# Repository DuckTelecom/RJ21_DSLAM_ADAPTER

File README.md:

# RJ21_DSLAM_ADAPTER

This is an adapter / breakout aimed for use with the Zyxel AAM1212 DSLAM modules used in the IES-1000 chassis.

It takes 24 lines in on the "EXCHANGE" side, breaks them out to the two RJ21 connectors on the DSLAM, then recombines 24 lines with ADSL on the the "DISTRIBUTION" side.

**Note: It's currently untested. I will update this repo once the board has been manufactured and tested**

## License

This project is licensed is licensed under the terms of the  _MIT license_.

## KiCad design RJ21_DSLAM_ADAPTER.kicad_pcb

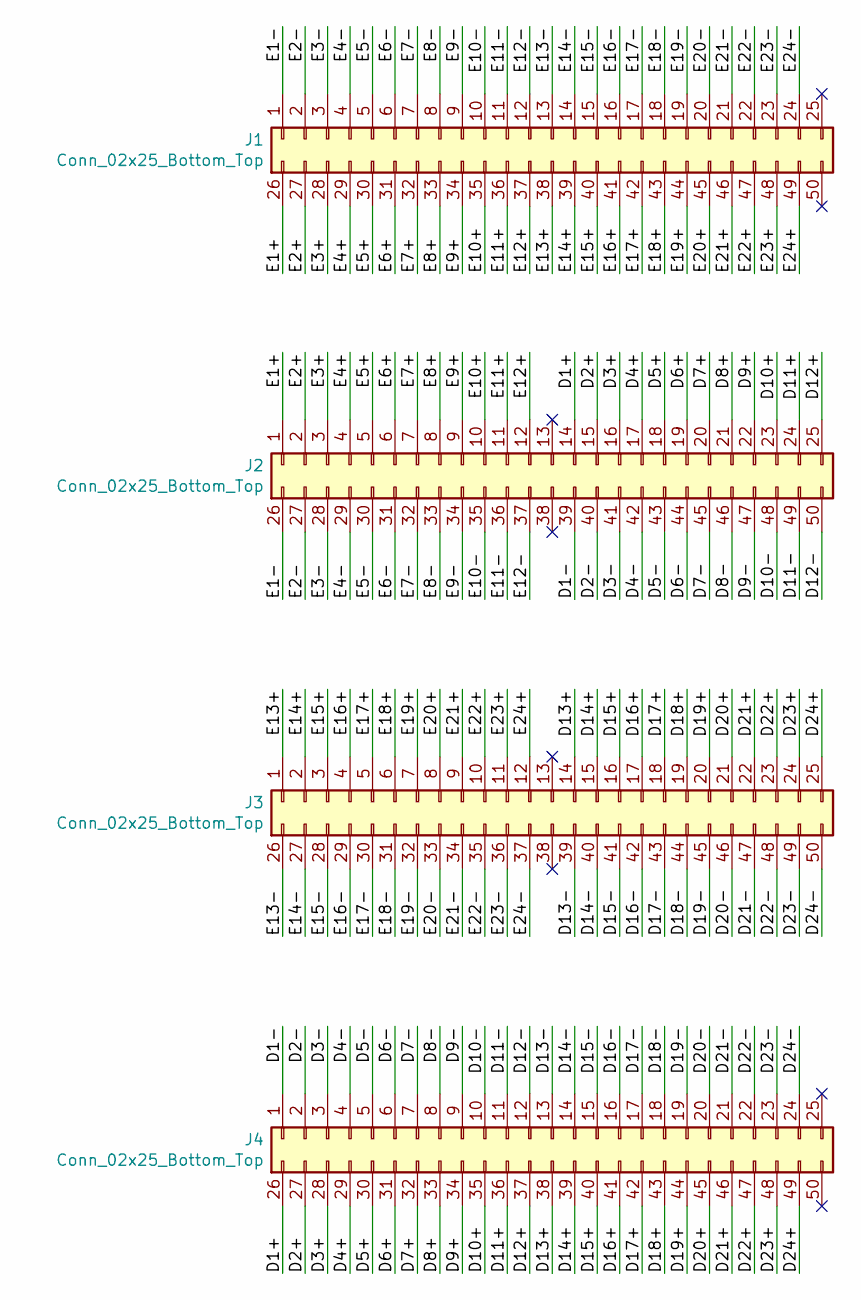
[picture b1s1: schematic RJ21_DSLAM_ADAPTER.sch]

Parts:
J1, J2, J3, J4: Conn_02x25_Bottom_Top; AliExpress_RJ21_PCB

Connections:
/D1+: J2.14, J4.26
/D1-: J2.39, J4.1
/D2+: J2.15, J4.27
/D2-: J2.40, J4.2
/D3+: J2.16, J4.28
/D3-: J2.41, J4.3
/D4+: J2.17, J4.29
/D4-: J2.42, J4.4
/D5+: J2.18, J4.30
/D5-: J2.43, J4.5
/D6+: J2.19, J4.31
/D6-: J2.44, J4.6
/D7+: J2.20, J4.32
/D7-: J2.45, J4.7
/D8+: J2.21, J4.33
/D8-: J2.46, J4.8
/D9+: J2.22, J4.34
/D9-: J2.47, J4.9
/D10+: J2.23, J4.35
/D10-: J2.48, J4.10
/D11+: J2.24, J4.36
/D11-: J2.49, J4.11
/D12+: J2.25, J4.37
/D12-: J2.50, J4.12
/D13+: J3.14, J4.38
/D13-: J3.39, J4.13
/D14+: J3.15, J4.39
/D14-: J3.40, J4.14
/D15+: J3.16, J4.40
/D15-: J3.41, J4.15
/D16+: J3.17, J4.41
/D16-: J3.42, J4.16
/D17+: J3.18, J4.42
/D17-: J3.43, J4.17
/D18+: J3.19, J4.43
/D18-: J3.44, J4.18
/D19+: J3.20, J4.44
/D19-: J3.45, J4.19
/D20+: J3.21, J4.45
/D20-: J3.46, J4.20
/D21+: J3.22, J4.46
/D21-: J3.47, J4.21
/D22+: J3.23, J4.47
/D22-: J3.48, J4.22
/D23+: J3.24, J4.48
/D23-: J3.49, J4.23
/D24+: J3.25, J4.49
/D24-: J3.50, J4.24
/E1+: J1.26, J2.1
/E1-: J1.1, J2.26
/E2+: J1.27, J2.2
/E2-: J1.2, J2.27
/E3+: J1.28, J2.3
/E3-: J1.3, J2.28
/E4+: J1.29, J2.4
/E4-: J1.4, J2.29
/E5+: J1.30, J2.5
/E5-: J1.5, J2.30
/E6+: J1.31, J2.6
/E6-: J1.6, J2.31
/E7+: J1.32, J2.7
/E7-: J1.7, J2.32
/E8+: J1.33, J2.8
/E8-: J1.8, J2.33
/E9+: J1.34, J2.9
/E9-: J1.9, J2.34
/E10+: J1.35, J2.10
/E10-: J1.10, J2.35
/E11+: J1.36, J2.11
/E11-: J1.11, J2.36
/E12+: J1.37, J2.12
/E12-: J1.12, J2.37
/E13+: J1.38, J3.1
/E13-: J1.13, J3.26
/E14+: J1.39, J3.2
/E14-: J1.14, J3.27
/E15+: J1.40, J3.3
/E15-: J1.15, J3.28
/E16+: J1.41, J3.4
/E16-: J1.16, J3.29
/E17+: J1.42, J3.5
/E17-: J1.17, J3.30
/E18+: J1.43, J3.6
/E18-: J1.18, J3.31
/E19+: J1.44, J3.7
/E19-: J1.19, J3.32
/E20+: J1.45, J3.8
/E20-: J1.20, J3.33
/E21+: J1.46, J3.9
/E21-: J1.21, J3.34
/E22+: J1.47, J3.10
/E22-: J1.22, J3.35
/E23+: J1.48, J3.11
/E23-: J1.23, J3.36
/E24+: J1.49, J3.12
/E24-: J1.24, J3.37

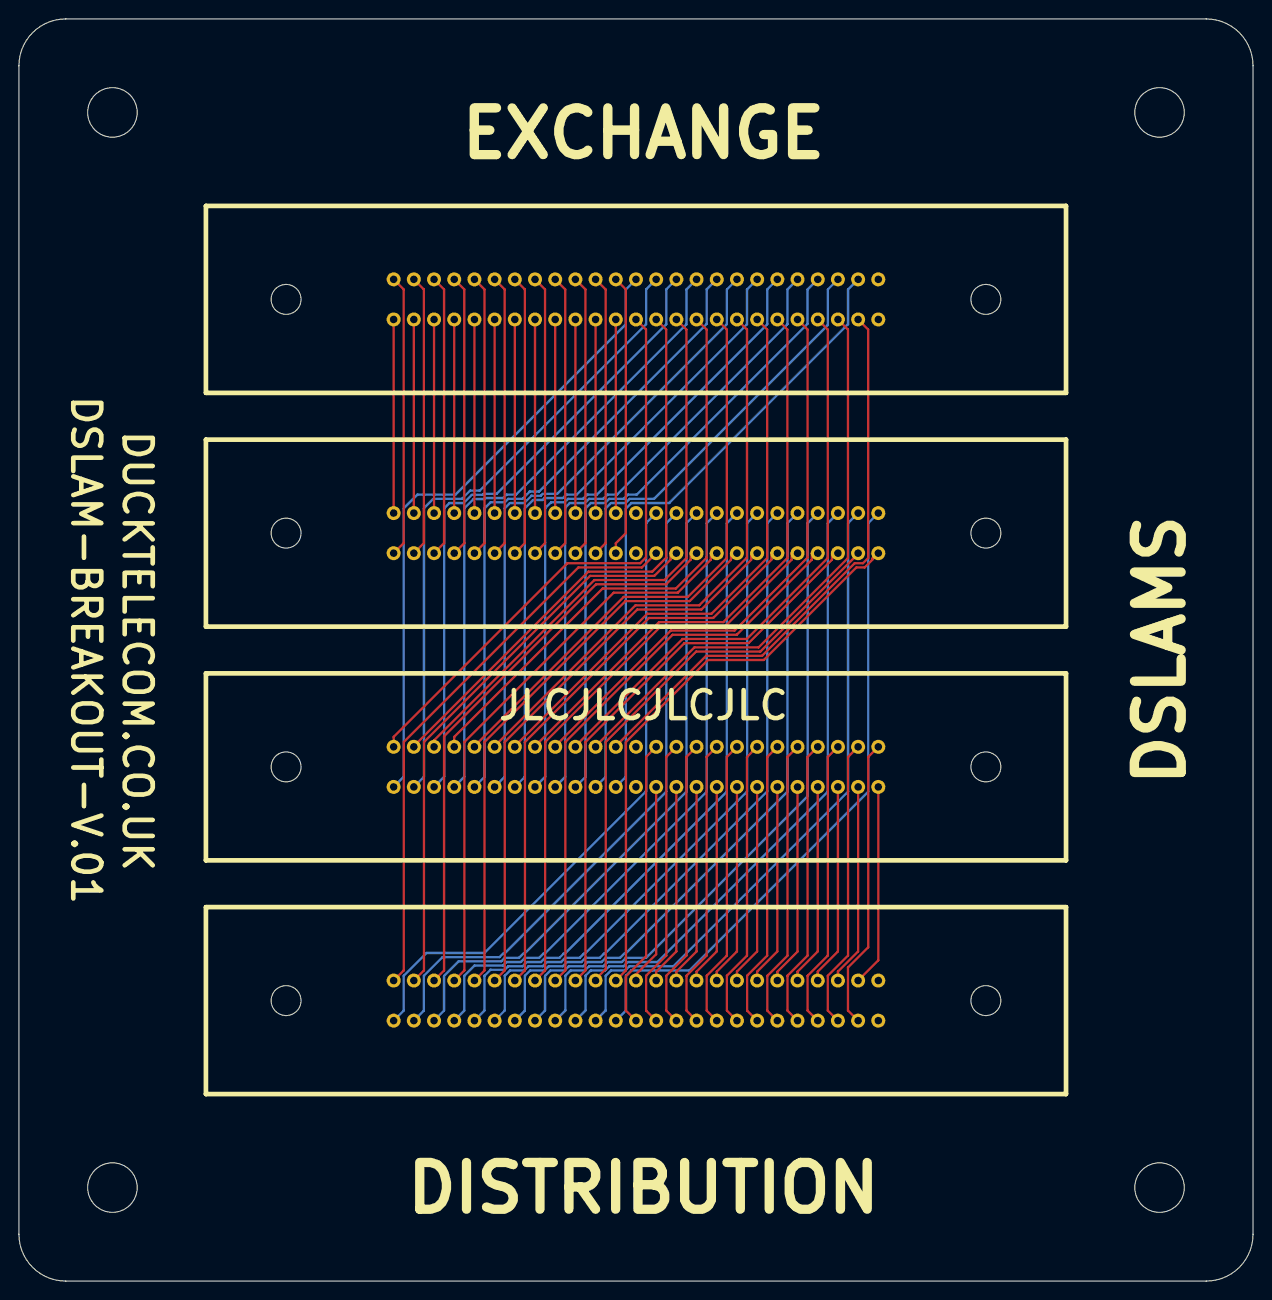
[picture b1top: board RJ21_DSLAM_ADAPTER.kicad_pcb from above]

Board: 2 copper layers, 132.0 x 135.0 mm, 4 parts (0 on the bottom side), 96 nets.
